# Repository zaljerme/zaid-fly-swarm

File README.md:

# Zaid Fly: a 20-drone ESP32 swarm

<p align="center">
  <b>20 palm-sized drones · 1 ground station · 1 radio frame per update · no noticeable lag</b><br>
  Custom PCB · hand-soldered · 3D-printed frames · ESP-NOW swarm firmware
</p>

---

## The goal

I wanted to fly **20 drones at once from one controller with no delay you can notice**, and have every drone react **at the same instant**, so the swarm moves as one object instead of 20 drones each catching up at their own pace.

Most hobby swarms send one message per drone. With 20 drones the last one hears its command several milliseconds after the first, and every lost packet triggers a retry that adds more delay. I built Zaid Fly around one idea: **put the whole swarm's commands in a single broadcast radio frame.** One frame on the air, 20 drones receive it together, and each one reads its own 8-byte slot.

## What I did

| | |
|---|---|
| **Designed the electronics** | A carrier PCB for the Seeed XIAO ESP32-S3 with an MPU-6050 IMU, four SI2300 MOSFET motor drivers with flyback protection, a battery-sense divider, status LEDs, and headlights and taillights. KiCad files are in [`hardware/`](hardware/). |
| **Ordered the components** | 20 sets of everything plus spares (full list below and in [`hardware/bom/zaid-fly-bom.csv`](hardware/bom/zaid-fly-bom.csv)). |
| **Soldered 20 boards by hand** | 45 parts per board, 900 parts total, including the 4×4 mm QFN IMU. |
| **3D-printed 20 frames and covers** | Frame, cover and alternative frames are in [`3d-models/`](3d-models/). |
| **Wrote the firmware** | A 1 kHz flight controller for every drone and a 200 Hz ground-station radio bridge. Both are in [`firmware/`](firmware/). |
| **Wrote the swarm controller** | PC software for flying with a gamepad, running light shows and measuring latency. It's in [`software/`](software/). |

## Build gallery

| Components for one drone | Schematic |
|---|---|
|  |  |

| PCB placement | PCB routed (GND pour) |
|---|---|
|  |  |

| Generated board (top) | Ratsnest from the netlist |
|---|---|
|  |  |

| 3D-printed frame | Full assembly |
|---|---|
|  |  |

<p align="center">
  <br>
  <i>The 20 nodes, IDs 00–19, rendered from the STL files in this repo.</i>
</p>

---

## How the "no delay" link works

1. **The PC** reads the gamepad and sends the full 20-slot command table over USB at 100 Hz.
2. **The ground station** (an XIAO ESP32-S3) stores the table and broadcasts it on its own **hardware-timed 200 Hz clock**, so timing jitter on the PC side never reaches the drones.
3. **One ESP-NOW broadcast frame** (172 bytes: header plus 20 × 8-byte slots) goes out every 5 ms on a fixed channel at a fixed 6 Mbps PHY rate:
   * **No ACKs and no retries.** A late command is worse than a lost one, and the next frame is only 5 ms away.
   * **Wi-Fi power-save is off** on every node, so the radio never dozes between frames.
   * **All 20 drones hear the same frame at the same instant**, so the swarm stays in sync by construction.
4. **Each drone** copies its slot in the Wi-Fi callback and its **1 kHz control loop** uses it within 1 ms.
5. **Telemetry uses TDMA.** Drone *N* only replies to the frame where `seq % 20 == N`. Each drone reports at 10 Hz, and replies never collide with each other or with the command stream. Every reply echoes the ground station's timestamp, so round-trip time is measured continuously.

| Stage | Budget |
|---|---|
| PC loop + USB CDC | ≤ 10 ms (typically ~1 ms) |
| Wait for the next 200 Hz TX tick | ≤ 5 ms (2.5 ms average) |
| Airtime, 172 B @ 6 Mbps | ~0.35 ms |
| Wait for the next 1 kHz control tick + compute | ≤ 1.5 ms |
| **Stick to motor (typical / worst case)** | **~5 ms / ~17 ms** |

People start noticing control lag at about 50 ms. The design stays well under that, with the same delay for all 20 drones.

**Measured on my swarm** (run `python software/swarm_controller.py --port COMx --mode latency`):

| Metric | Result |
|---|---|
| Median round-trip time (GS → drone → GS) | _fill in_ |
| 95th-percentile RTT | _fill in_ |
| Lost frames per drone (indoor, 3 m) | _fill in_ |
| Worst control-loop time | _fill in_ |

More detail: [`docs/LOW_LATENCY.md`](docs/LOW_LATENCY.md)

---

## Hardware

### Pin map (XIAO ESP32-S3)

| XIAO | GPIO | Function |
|---|---|---|
| D0–D3 | 1–4 | Motor 1–4 MOSFET gates (20 kHz PWM) |
| D4 / D5 | 5 / 6 | I²C SDA / SCL → MPU-6050 (10k pull-ups) |
| D6 | 43 | Red status LED |
| D7 | 44 | Green status LED |
| D8 | 7 | Headlights (2× white) |
| D9 | 8 | Taillights (2× red) |
| D10 | 9 | Battery sense (VBAT ÷ 2) |

Motor layout (top view, front up): **M4** front-left CW · **M1** front-right CCW · **M3** rear-left CCW · **M2** rear-right CW.

### Bill of materials

**Per drone** (the electronics come from [`zaid-fly-bom.csv`](hardware/bom/zaid-fly-bom.csv), which is generated from the netlist):

| Qty | Part | Notes |
|---|---|---|
| 1 | Seeed Studio XIAO ESP32-S3 | MCU and radio. Its built-in charger and LDO run it from the LiPo |
| 1 | Zaid Fly carrier PCB | 28 × 38 mm, 2-layer, 1.0 mm FR-4 |
| 1 | MPU-6050 (QFN-24) | 6-axis IMU |
| 4 | SI2300 N-MOSFET (SOT-23) | Low-side motor switches |
| 4 | 1N4148WS (SOD-323) | Motor flyback diodes |
| 6 | 0.1 µF 0603 | 4 across the motors, MPU VDD and REGOUT |
| 2 | 0.01 µF 0603 | MPU CPOUT and VLOGIC |
| 9 | 10 kΩ 0603 | Gate pull-downs, I²C pull-ups, AD0, battery divider |
| 2 / 2 / 2 | 100 Ω / 150 Ω / 200 Ω 0603 | LED resistors |
| 3 / 1 / 2 | Red / green / white 0603 LEDs | Status, taillights, headlights |
| 4 | 720 coreless brushed motors (7 × 20 mm) | 2 CW + 2 CCW |
| 4 | 31 mm propellers | 2 A + 2 B |
| 1 | 1S 3.7 V LiPo, ~250–300 mAh, JST-PH 2.0 | |
| 1 | 3D-printed frame + cover | [`3d-models/stl`](3d-models/stl) |
| 2 | 1×7 low-profile pin headers | Stack the XIAO above the SMD parts |

**For the whole project** (20 drones plus the ground station):

| Qty | Item |
|---|---|
| 21 | XIAO ESP32-S3 (20 drones + 1 ground station, which should have the external U.FL antenna) |
| 20 (+5 spare) | Carrier PCBs |
| 20 (+2) | MPU-6050 |
| 80 (+10) | SI2300, 1N4148WS |
| 120 / 40 | 0.1 µF / 0.01 µF capacitors |
| 180 / 40 / 40 / 40 | 10k / 100 Ω / 150 Ω / 200 Ω resistors |
| 60 / 20 / 40 | Red / green / white LEDs |
| 80 (+8) | 720 coreless motors (40 CW, 40 CCW) |
| 80 (+20) | 31 mm props (40 A, 40 B) |
| 20 (+10) | 1S LiPo batteries + a multi-port 1S charger |
| ~250 g | PLA or PETG for 20 frames and covers |
| 1 | Big latching E-STOP button for the ground station |
| | Solder paste, flux, hot-air station, fine-tip iron, tweezers, magnifier, 30 AWG silicone wire |

---

## 3D-printed parts

| File | What it is |
|---|---|
| [`zaid-fly-frame.stl`](3d-models/stl/zaid-fly-frame.stl) | Main frame used for the swarm (47.8 × 47.8 mm) |
| [`zaid-fly-cover.stl`](3d-models/stl/zaid-fly-cover.stl) | Top cover with the **ZAID FLY** label |
| [`zaid-fly-camera-cover.stl`](3d-models/stl/zaid-fly-camera-cover.stl) | Cover variant with a camera mount (XIAO ESP32-S3 Sense) |
| [`zaid-fly-60mm-brushed-extended-frame.stl`](3d-models/stl/zaid-fly-60mm-brushed-extended-frame.stl) | Extended-arm frame for bigger props |
| [`zaid-fly-brushless-extended-frame.stl`](3d-models/stl/zaid-fly-brushless-extended-frame.stl) | Extended-arm frame for brushless motors |

STEP files for editing are in [`3d-models/step/`](3d-models/step/). Print settings and credits are in [`3d-models/README.md`](3d-models/README.md).

---

## Repository layout

```
zaid-fly-swarm/
├── firmware/
│   ├── common/swarm_protocol.h     # radio + USB protocol shared by every node
│   ├── drone/                      # flight controller (PlatformIO, XIAO ESP32-S3)
│   └── ground_station/             # USB <-> ESP-NOW 200 Hz broadcaster
├── software/swarm_controller.py    # PC: gamepad / lights / latency modes
├── hardware/
│   ├── kicad/                      # KiCad 8 project, symbols, footprints, netlist
│   ├── bom/zaid-fly-bom.csv
│   └── tools/generate_kicad.py     # netlist + placement source of truth
├── 3d-models/{stl,step}/           # frame and cover files
├── docs/                           # build guide, latency notes, images
└── tools/render_images.py          # regenerates the renders in docs/images
```

## Quick start

```bash
# 1. Flash every drone (same binary for all 20)
cd firmware/drone && pio run -t upload
# 2. Give each drone its swarm ID (0-19): open the serial monitor and type   id 7
pio device monitor
# 3. Flash the ground station
cd ../ground_station && pio run -t upload
# 4. Run the swarm
cd ../../software && pip install -r requirements.txt
python swarm_controller.py --port COM5 --mode lights     # check all 20 nodes respond
python swarm_controller.py --port COM5 --mode latency    # measure the link
python swarm_controller.py --port COM5 --mode gamepad    # fly
```

The full step-by-step guide (ordering, soldering, printing, assembly, tuning, and bringing up all 20 drones) is in **[`docs/BUILD_GUIDE.md`](docs/BUILD_GUIDE.md)**.

## Safety features

* **E-STOP**: SPACE, gamepad **B**, Ctrl+C or the hardware button on the ground station kills every motor in the swarm. The hardware stop latches until reboot.
* **Link loss**: if a drone hears nothing for 150 ms, it levels out and ramps throttle to zero over 2.5 s.
* **PC crash**: the ground station stops transmitting after 300 ms, so every drone runs its own failsafe landing.
* **Crash detection**: tilt beyond 70° cuts the motors.
* **Arming**: a drone only arms with a live link and throttle at the bottom.
* **Battery compensation**: motor output is scaled for battery sag, so a drone on a 3.6 V pack responds the same as one on a fresh 4.2 V pack.

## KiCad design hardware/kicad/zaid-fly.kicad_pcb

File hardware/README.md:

# Zaid Fly carrier PCB (rev A)

28 × 38 mm, 2-layer, 1.0 mm FR-4. The XIAO ESP32-S3 sits on low-profile headers **above** the SMD parts, so the whole flight controller fits on a footprint not much bigger than the XIAO.

## Files

| Path | What |
|---|---|
| `kicad/zaid-fly.kicad_pro` | KiCad 8 project (open this) |
| `kicad/zaid-fly.kicad_sch` | Schematic. Every pin is tied to its net with a label |
| `kicad/zaid-fly.kicad_pcb` | Board: outline, all 45 footprints placed, nets assigned, GND pours on both layers |
| `kicad/ZaidFly.kicad_sym`, `kicad/ZaidFly.pretty/` | Project symbol and footprint libraries (registered in the local lib tables) |
| `kicad/NETLIST.md` | Readable net-by-net connection list |
| `bom/zaid-fly-bom.csv` | BOM with per-drone and ×20 quantities |
| `tools/generate_kicad.py` | **Source of truth**: netlist + placement → all files above + renders |

To change a part value, net or position, edit `generate_kicad.py` and run:

```bash
python hardware/tools/generate_kicad.py
```

It also runs a courtyard-overlap and board-edge check before writing anything.

## Circuit

| Block | Parts | Notes |
|---|---|---|
| MCU | U2 XIAO ESP32-S3 | Runs from the 1S LiPo through its BAT pads (J2 link) and built-in charger and LDO |
| IMU | U1 MPU-6050, C5–C8, R5–R7 | Decoupling per the datasheet (VDD 0.1 µF, REGOUT 0.1 µF, CPOUT 10 nF, VLOGIC 10 nF). AD0 pulled low → address 0x68 |
| Motor drivers ×4 | Q1–Q4 SI2300, D1–D4 1N4148WS, C1–C4 0.1 µF, R1–R4 10k | Low-side switch. The flyback diode and cap sit right across each motor. The 10k pull-down keeps the gates off during boot |
| Battery sense | R8/R9 10k/10k | VBAT ÷ 2 → GPIO9 (ADC1) |
| Lights | D5–D10 + R10–R15 | Status red and green, 2× white headlights, 2× red taillights |

## Routing notes

The board ships placed with nets assigned. Route it in KiCad, or run Freerouting through the KiCad plugin and then tidy up by hand:

* **Power** net class (already in the project): VBAT, GND, MOT1-…MOT4- at **0.6 mm**. Each motor pulls about 1 A peak.
* Keep each motor loop (VBAT → motor → MOSFET → GND) short and right next to its diode and cap.
* Run I²C (SDA and SCL) under the XIAO, away from the motor drain traces.
* Stitch the top and bottom GND pours with vias around the IMU, then press **B** to refill zones before DRC.
* Signals: 0.2 mm track and 0.15 mm clearance. Vias are 0.6/0.3 mm, which every common board house can make.

## Fab settings

2 layers · 1.0 mm · ENIG · green mask, white silk · order a stencil · 25 pcs.

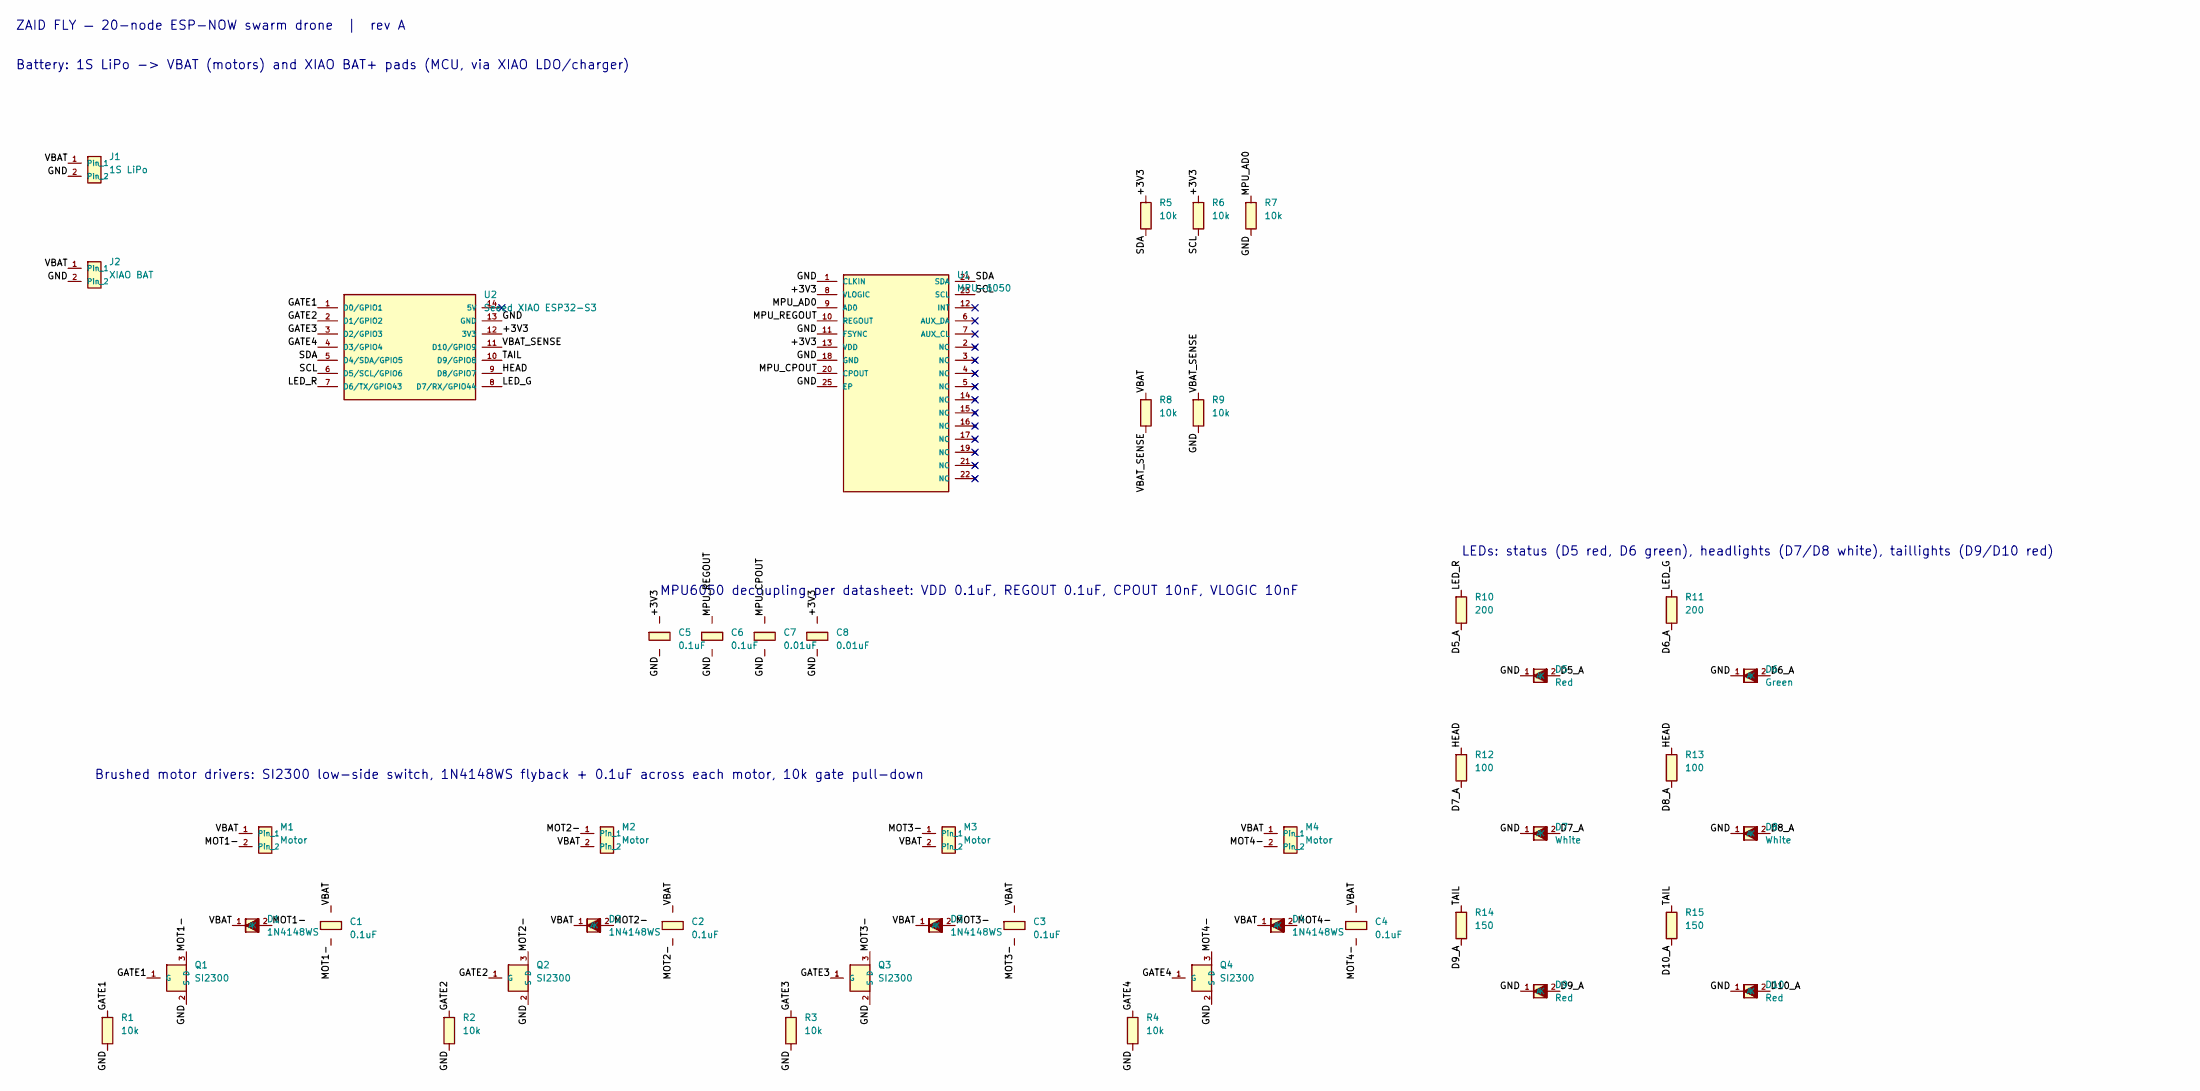
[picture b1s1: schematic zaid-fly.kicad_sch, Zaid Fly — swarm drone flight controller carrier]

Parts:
C1, C2, C3, C4, C5, C6: 0.1uF; C_0603; MPN 0603 X7R 16V (C14663)
C7, C8: 0.01uF; C_0603; MPN 0603 X7R 50V (C57112)
D1, D2, D3, D4: 1N4148WS; D_SOD-323; MPN 1N4148WS flyback (C2128)
D5, D9, D10: Red; LED_0603; MPN 0603 red LED (C2286)
D6: Green; LED_0603; MPN 0603 green LED (C72043)
D7, D8: White; LED_0603; MPN 0603 white LED (C2290)
J1: 1S LiPo; Pad_2x_1.7mm_H; MPN JST-PH 2.0 pigtail, 1S 3.7V
J2: XIAO BAT; Pad_2x_1.7mm_H; MPN wire link to XIAO BAT+/BAT- pads
M1, M2, M3, M4: Motor; Pad_2x_1.7mm; MPN 720 coreless brushed motor (7x20 mm)
Q1, Q2, Q3, Q4: SI2300; SOT-23; MPN SI2300 N-MOSFET (C10487)
R1, R2, R3, R4: 10k; R_0603; MPN 0603 1% gate pull-down (C25804)
R5, R6, R7, R8, R9: 10k; R_0603; MPN 0603 1% (C25804)
R10, R11: 200; R_0603; MPN 0603 1%
R12, R13: 100; R_0603; MPN 0603 1%
R14, R15: 150; R_0603; MPN 0603 1%
U1: MPU-6050; QFN-24_4x4mm_P0.5mm; MPN TDK InvenSense MPU-6050 (LCSC C24112)
U2: Seeed XIAO ESP32-S3; XIAO_ESP32S3_THT; MPN Seeed 113991114

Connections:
+3V3: C5.1, C8.1, R5.1, R6.1, U1.8 (VLOGIC), U1.13 (VDD), U2.12 (3V3)
D5_A: D5.2 (A), R10.2
D6_A: D6.2 (A), R11.2
D7_A: D7.2 (A), R12.2
D8_A: D8.2 (A), R13.2
D9_A: D9.2 (A), R14.2
D10_A: D10.2 (A), R15.2
GATE1: Q1.1 (G), R1.1, U2.1 (D0/GPIO1)
GATE2: Q2.1 (G), R2.1, U2.2 (D1/GPIO2)
GATE3: Q3.1 (G), R3.1, U2.3 (D2/GPIO3)
GATE4: Q4.1 (G), R4.1, U2.4 (D3/GPIO4)
GND: C5.2, C6.2, C7.2, C8.2, D5.1 (K), D6.1 (K), D7.1 (K), D8.1 (K), D9.1 (K), D10.1 (K), J1.2, J2.2, Q1.2 (S), Q2.2 (S), Q3.2 (S), Q4.2 (S), R1.2, R2.2, R3.2, R4.2, R7.2, R9.2, U1.1 (CLKIN), U1.11 (FSYNC), U1.18 (GND), U1.25 (EP), U2.13 (GND)
HEAD: R12.1, R13.1, U2.9 (D8/GPIO7)
LED_G: R11.1, U2.8 (D7/RX/GPIO44)
LED_R: R10.1, U2.7 (D6/TX/GPIO43)
MOT1-: C1.2, D1.2 (A), M1.2, Q1.3 (D)
MOT2-: C2.2, D2.2 (A), M2.1, Q2.3 (D)
MOT3-: C3.2, D3.2 (A), M3.1, Q3.3 (D)
MOT4-: C4.2, D4.2 (A), M4.2, Q4.3 (D)
MPU_AD0: R7.1, U1.9 (AD0)
MPU_CPOUT: C7.1, U1.20 (CPOUT)
MPU_REGOUT: C6.1, U1.10 (REGOUT)
SCL: R6.2, U1.23 (SCL), U2.6 (D5/SCL/GPIO6)
SDA: R5.2, U1.24 (SDA), U2.5 (D4/SDA/GPIO5)
TAIL: R14.1, R15.1, U2.10 (D9/GPIO8)
VBAT: C1.1, C2.1, C3.1, C4.1, D1.1 (K), D2.1 (K), D3.1 (K), D4.1 (K), J1.1, J2.1, M1.1, M2.2, M3.2, M4.1, R8.1
VBAT_SENSE: R8.2, R9.1, U2.11 (D10/GPIO9)

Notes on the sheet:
ZAID FLY — 20-node ESP-NOW swarm drone | rev A
Battery: 1S LiPo -> VBAT (motors) and XIAO BAT+ pads (MCU, via XIAO LDO/charger)
Brushed motor drivers: SI2300 low-side switch, 1N4148WS flyback + 0.1uF across each motor, 10k gate pull-down
LEDs: status (D5 red, D6 green), headlights (D7/D8 white), taillights (D9/D10 red)
MPU6050 decoupling per datasheet: VDD 0.1uF, REGOUT 0.1uF, CPOUT 10nF, VLOGIC 10nF

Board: 2 copper layers, 45 parts (0 on the bottom side), 27 nets, no tracks yet.

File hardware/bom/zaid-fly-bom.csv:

References,Value,Footprint,Part / notes,Qty per drone,Qty for 20 drones
C1 C2 C3 C4 C5 C6,0.1uF,C_0603,0603 X7R 16V,6,120
C7 C8,0.01uF,C_0603,0603 X7R 50V,2,40
D1 D2 D3 D4,1N4148WS,D_SOD-323,1N4148WS flyback (C2128),4,80
D5 D9 D10,Red,LED_0603,0603 red LED (C2286),3,60
D6,Green,LED_0603,0603 green LED (C72043),1,20
D7 D8,White,LED_0603,0603 white LED (C2290),2,40
J1,1S LiPo,Pad_2x_1.7mm_H,"JST-PH 2.0 pigtail, 1S 3.7V",1,20
J2,XIAO BAT,Pad_2x_1.7mm_H,wire link to XIAO BAT+/BAT- pads,1,20
M1 M2 M3 M4,Motor,Pad_2x_1.7mm,720 coreless brushed motor (7x20 mm),4,80
Q1 Q2 Q3 Q4,SI2300,SOT-23,SI2300 N-MOSFET (C10487),4,80
R1 R2 R3 R4,10k,R_0603,0603 1% gate pull-down,4,80
R5 R6 R7 R8 R9,10k,R_0603,0603 1%,5,100
R10 R11,200,R_0603,0603 1%,2,40
R12 R13,100,R_0603,0603 1%,2,40
R14 R15,150,R_0603,0603 1%,2,40
U1,MPU-6050,QFN-24_4x4mm_P0.5mm,TDK InvenSense MPU-6050 (LCSC C24112),1,20
U2,Seeed XIAO ESP32-S3,XIAO_ESP32S3_THT,Seeed 113991114,1,20

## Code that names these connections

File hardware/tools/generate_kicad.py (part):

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    "Conn_01x02": ((-1.27, 1.27, 1.27, -3.81), [("1", "Pin_1", -5.08, 0, 0, "passive"),
                                                ("2", "Pin_2", -5.08, -2.54, 0, "passive")]),
}
_xiao_names = ["D0/GPIO1", "D1/GPIO2", "D2/GPIO3", "D3/GPIO4", "D4/SDA/GPIO5", "D5/SCL/GPIO6",
               "D6/TX/GPIO43", "D7/RX/GPIO44", "D8/GPIO7", "D9/GPIO8", "D10/GPIO9", "3V3", "GND", "5V"]
SYMBOLS["XIAO_ESP32S3"] = ((-12.7, 10.16, 12.7, -10.16),
                           [(str(i + 1), _xiao_names[i], -17.78, 7.62 - i * 2.54, 0, "bidirectional") for i in range(7)] +
                           [(str(i + 8), _xiao_names[i + 7], 17.78, -7.62 + i * 2.54, 180,
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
